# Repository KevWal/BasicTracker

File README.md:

# BasicTracker
Light weight long run time cheap tracker

# Hardware

## Power
Single AA or AAA cell, 0.8v to 1.6v input range - TPS61200 to boost to 1.8 or 3.3v

Solar Panel, 0.5v to 4.2v input range - either connect direct or use TPS61200 to boost or limit or MCP1700T to limit to 1.8 or 3.3v

Single AA or AAA cell and Solar Panel, needs 2 x MAX40200 ideal diodes to keep supplies separate and TPS61200 to boost or limit to 1.8v or 3.3v
	Primary cells will keep tracker going over night till battery runs out

Single Lithium, 2.8v to 4.2v useful range, needs Battery Protection on Lipo to limit min discharge voltage and MCP1700T to limit to 1.8 or 3.3v
	Will likely freeze at night

Single Lithium and Solar Panel, Solar Panel needs TPS61200 to stop lithium discharging through it and buck/boost voltage to max 4.2v for Lithium charging.  Lithium needs Battery Protection to limit min discharge voltage and MCP1700T to limit to 1.8 or 3.3v. Lithium will likely freeze at night.

### Boost Converter
Boost converter to 1.8v with 3.3v and 4.2v (for lithium charge) option

Step ups in stock with JLC:
L6920DBTR - $1.40 RP Protect, Min startup for 3.3vout@40mA = 0.72v
TPS61220DCKR - $0.49 Min startup for 3.3vout@40mA = 0.7v
TLV61220DBVR - $0.26. Min startup for 3.3vout@40mA = 0.7v
*TPS61200DRC - $0.85.  Min startup for 3.3vout@40mA = 0.4v, max 150mA at 0.7v in*

#### Inductor
*SMD_Murata-Electronics-1227AS-H-2R2M-P2_C435389*

### Voltage Measuring
Measure Battery, Solar and Lithium voltages

## GPS Module
Ublox Max 6G 1.75v to 2.0v
Ublox Max 7C / M8C 1.65v to 3.6v
Ublox Max M8Q 2.7v to 3.6v

ATGM336N 2.7v to 3.6v.
Quectel L70 2.8v to 4.3v

Connected I2C, PPS, Battery Backup, etc
Battery backup via resistor, capacitor and diode
Antenna Options - Chip, Wire, static leak resister option

### GPS Power Switch
*SIP32431DR3-T1GE3 - instock in JLC*

### GPS Filtering
*MuRata_BLM15HD102SN1D_1kR-25-at100MHz-250mA_C21516*

### GPS Antenna
1/4 wave wire = 45.2mm (1575Mhz) (1/4 wave generally better than chip antenna IMO)

## Processor
ATMega1284p - In stock in JLC, 10mmx10mm, 128kb of storage, 16kb of ram
	Step up from 328 but still same family
	JTAG interface not one wire debug.
	Info on using the 1284 - https://prominimicros.com/
	Arduino Core - https://github.com/MCUdude/MightyCore
4Mhz crystal (max at 1.8v) and option to use /8 fuse.

Move to a ATSAMD21G18A-AU or similar?  Still arduinio compatible but so much more powerful.
	ARM Cortex SWD interface?  Built in RTC.  Not instock with JLC

STM xx?
Ideally would get a USB Interface, but no easy in JLC stock way found.

### Crystal
XXFEELNANF-14.7456M & 16pF.  Divide by 8 to get 1.843200Mhz and use 115,200 comms

## Fuses
Extended = 0xFF
High = 0x16
Low = 0x7F (ck div 8 set)

Arduino
	Clock External 14.7456 (even though clk/8 fuse set)?

## Radio
SX1278 (137-525MHz) on the DORJI DRF1278F module - http://www.dorji.com/products-detail.php?ProId=14
	1.8v to 3.6v, < 1uA standby

or

Hope RF RFM98W - 433MHz band
https://www.hoperf.com/modules/lora/RFM98.html
	1.8v to 3.7v, < 1uA standby

# IDE
Move away from Arduinio V1?

Mightcore for ATMega1284p - https://github.com/MCUdude/MightyCore

Arduino V2 - https://www.arduino.cc/en/Tutorial/getting-started-with-ide-v2
Visual Micro - Arduino for Visual Studio - https://www.visualmicro.com/
PlatformIO IDE - Arduino and Visual Studio Code - https://platformio.org/

## Arduino V2
Too add the AVR Dragon programmer, add the below to:

C:\Users\WALTONK\AppData\Local\Arduino15\packages\MightyCore\hardware\avr\2.1.2\programmers.txt

dragon_jtag.name=Dragon JTAG (KW)
dragon_jtag.communication=usb
dragon_jtag.protocol=dragon_jtag
dragon_jtag.program.protocol=dragon_jtag
dragon_jtag.program.tool=avrdude
dragon_jtag.program.extra_params=-P usb

## Microchip Studio
Good Device Programming interface for fuses
Works with:
	Pololu USB AVR (STK500) - can supply / program at 3.3 or 5v; and
	AVR Dragon - can supply 5v, can program down to 1.8v

# Others Projects
UPU's original 1.8v 4Mhz - https://ava.upuaut.net/?p=383 https://ava.upuaut.net/?p=353
	RFM22B

# Code Research
Dave's flexavr - https://github.com/daveake/flexavr
	Designed for Standalone AVR attached to a Pi Zero
	APRS via PWM to radio module, LoRa via RFM98W (sx1278, no library, direct register writes), Some RTTY functions, but doesn't seem complete?

OK1CDJ Picotracker - https://github.com/ok1cdj/Picotracker/blob/master/sw/picotracker.ino
	RTTY via RFM22 only, but useful power saving code.

Dave's FlexTrack - https://github.com/daveake/FlexTrack
	APRS via PWM to radio module, RTTY via Radiometrix MTX2 or Lora, LoRa via RFM98W (sx1278) 
	No library, direct register writes, spread across multiple ino's
	Onboard landing position prediction
	
Dave's FlexTrack TTGO - https://github.com/daveake/FlexTrack_TTGO
	As above, designed for TTGO board, LoRa & RTTY

*RoelKroes TB Tracker -  https://github.com/RoelKroes/TBTracker*
	RTTY and LoRa via SX127x (or Hope RFM9x)
	Uses RadioLib - https://github.com/jgromes/RadioLib and tinyGPS++ https://github.com/mikalhart/TinyGPSPlus
		Radiolib supports SX126/7/8x, RFM9x and many others, supports RTTY, Morse, SSTV, Hellschreiber, LoRa and support for LoRaWAN and APRS in discussion, but complex
	Has sleep functionality, nicely laid out

Stuarts HAB2 code - https://github.com/StuartsProjects/HAB2
	RTTY and Lora via SX126/7/8x
	Uses Stuarts SX12XX Library https://github.com/StuartsProjects/SX12XX-LoRa
	All in a single .ino and .h
	Has Upload command capability, Sleep, EEPROM config complexity
	Looks like the one file does command mode upload and tracker functionality

## The Things Network (TTN)
How about TTN upload too?

https://www.thethingsnetwork.org/docs/lorawan/frequency-plans/
EU 868, US 902, CN 470, AU 915, AS 923, etc

Steve G8KHW did a tracker based on xx but cant find the code?
	https://groups.google.com/g/ukhas/c/SxUo0VpO1XQ/m/mD6qNCW9BgAJ
	
Stuarts TTN code: https://github.com/StuartsProjects/TTN_GPS_Tracker
	Based on https://www.thethingsnetwork.org/labs/story/lorawan-gsp-tracker
	Uses the ATmega328P, RFM98 & LMIC library

Junior IOT code: https://github.com/JuniorIOT/GPS-Lora-Balloon-rfm95-TinyGPS
	Uses the ATmega328P, RFM95 & LMIC library
	
Nick's example of LMIC library on a 328p
	https://github.com/descartes/Arduino-LMIC-example
	
LMIC library https://github.com/matthijskooijman/arduino-lmic
	Supports SX1272 and SX1276 families (inc RFM92 and RFM95)
	
Adafruit TTN library: https://github.com/adafruit/TinyLoRa/

ICSpace Multi region TTN Tracker - https://github.com/ImperialSpaceSociety/picotracker-Lora
	Uses Murata ABZ LoRa Module (STM32 and LoRa radio combined)
	Updated TTNHABBridge - https://github.com/ImperialSpaceSociety/ttnhabbridge

Draguinio STM32 based TTN Tracker - https://www.tindie.com/products/edwin/lorawan-gps-tracker-with9-axis-accelerometer-lgt92/

http://revspace.nl/TTNHABBridge for uploader to HabHub

Needs dedicated LoraWAN reciever like:
Or could use LoRaGateway with this:  https://github.com/bokse001/dual_chan_pkt_fwd

## APRS
Can't do airbourne in the UK or on a UK call sign, 144Mhz, licensed spectrum

## Issues
Want to do RTTY, LoRa, APRS & LoRaWAN (TTN) from the same tracker.
LoRa HAB and RTTY are best done on 433Mhz license free, although could be done on 868Mhz
LoRaWAN has to be done on 868Mhz license free in Europe
APRS is on 144Mhz

HopeRF modules dont seem to have lower and upper band outputs connected to aerial?
RadioLib doesn't do APRS or LoRaWAN

## LoRa Modes

### From lora-gateway code:
Num; ImplicitOrExplicit; ErrorCoding; Bandwidth; SpreadingFactor; LowDataRateOptimize; BaudRate; Description
0: EXPLICIT_MODE, ERROR_CODING_4_8, BANDWIDTH_20K8, SPREADING_11, 1,    60, Telemetry - Normal mode for telemetry
1: IMPLICIT_MODE, ERROR_CODING_4_5, BANDWIDTH_20K8, SPREADING_6,  0,  1400, SSDV - Normal mode for SSDV
2: EXPLICIT_MODE, ERROR_CODING_4_8, BANDWIDTH_62K5, SPREADING_8,  0,  2000, Repeater - Normal mode for repeater network	
3: EXPLICIT_MODE, ERROR_CODING_4_6, BANDWIDTH_250K, SPREADING_7,  0,  8000, Turbo - Normal mode for high speed images in 868MHz band
4: IMPLICIT_MODE, ERROR_CODING_4_5, BANDWIDTH_250K, SPREADING_6,  0, 16828, TurboX - Fastest mode within IR2030 in 868MHz band
5: EXPLICIT_MODE, ERROR_CODING_4_8, BANDWIDTH_41K7, SPREADING_11, 0,   200, Calling - Calling mode
6: EXPLICIT_MODE, ERROR_CODING_4_5, BANDWIDTH_20K8, SPREADING_7,  0,  2800, Uplink - Uplink explicit mode (variable length)
7: IMPLICIT_MODE, ERROR_CODING_4_5, BANDWIDTH_41K7, SPREADING_6,  0,  2800, Uplink - Uplink mode for 868
8: EXPLICIT_MODE, ERROR_CODING_4_5, BANDWIDTH_20K8, SPREADING_7,  0,   910, Telnet - Telnet-style comms with HAB on 434
9: IMPLICIT_MODE, ERROR_CODING_4_5, BANDWIDTH_62K5, SPREADING_6,  0,  4500, SSDV Repeater - Fast (SSDV) repeater network

# Launch Announcement

Also testing some backup trackers:

Hoping to do a launch on Sunday (20th, tomorrow) morning, before 9am GMT from Northamptonshire, UK of a Yokohama Balloon, carrying a custom built 'Single AA' tracker based originally on the TBTracker code base, but heavily expanded and modified.

Looking to A) test my ability to get a Yokohama to float, and B) the custom tracker being able to be decoded across RTTY, LoRa and Horus FSK4.  Flight path is predicted to take it across Holland, Germany & maybe Poland - but with the weather systems all over the place at the moment, who knows! :)

The tracker is based on the ATmega1284 running at 1.8432Mhz, Ublox GPS and DRF1278 radio module, all with a 1.8v VCC.  About 25g with 1 x AA.

Yokohama is 48.6g and was pre stretched at 0.22PSI up to about 99" circumference and filled to 6g of free lift.

RTTY - KW-BCK1 - 50 Baud, 8n2, 610Hz shift, 434.113Mhz, 1 short sentence repeated 3 times every once every 2 minutes
	RX Frequency for me was about 434.084Mhz

LoRa - KW-BCK2 - Mode 5, 433.650Mhz, 1 sentence repeated 3 times every once every 2 minutes
	Field String of 0123456AI9, RX frequency for me of 433.653

Horus FSK4 - G7PMO-V2 - 100 Baud, 244Hz shift, 434.340Mhz, 1 binary packet repeated 3 times every once every 2 minutes
	RX frequency for me was about 434.312Mhz
	
Weight

28g + 6g free lift = 34

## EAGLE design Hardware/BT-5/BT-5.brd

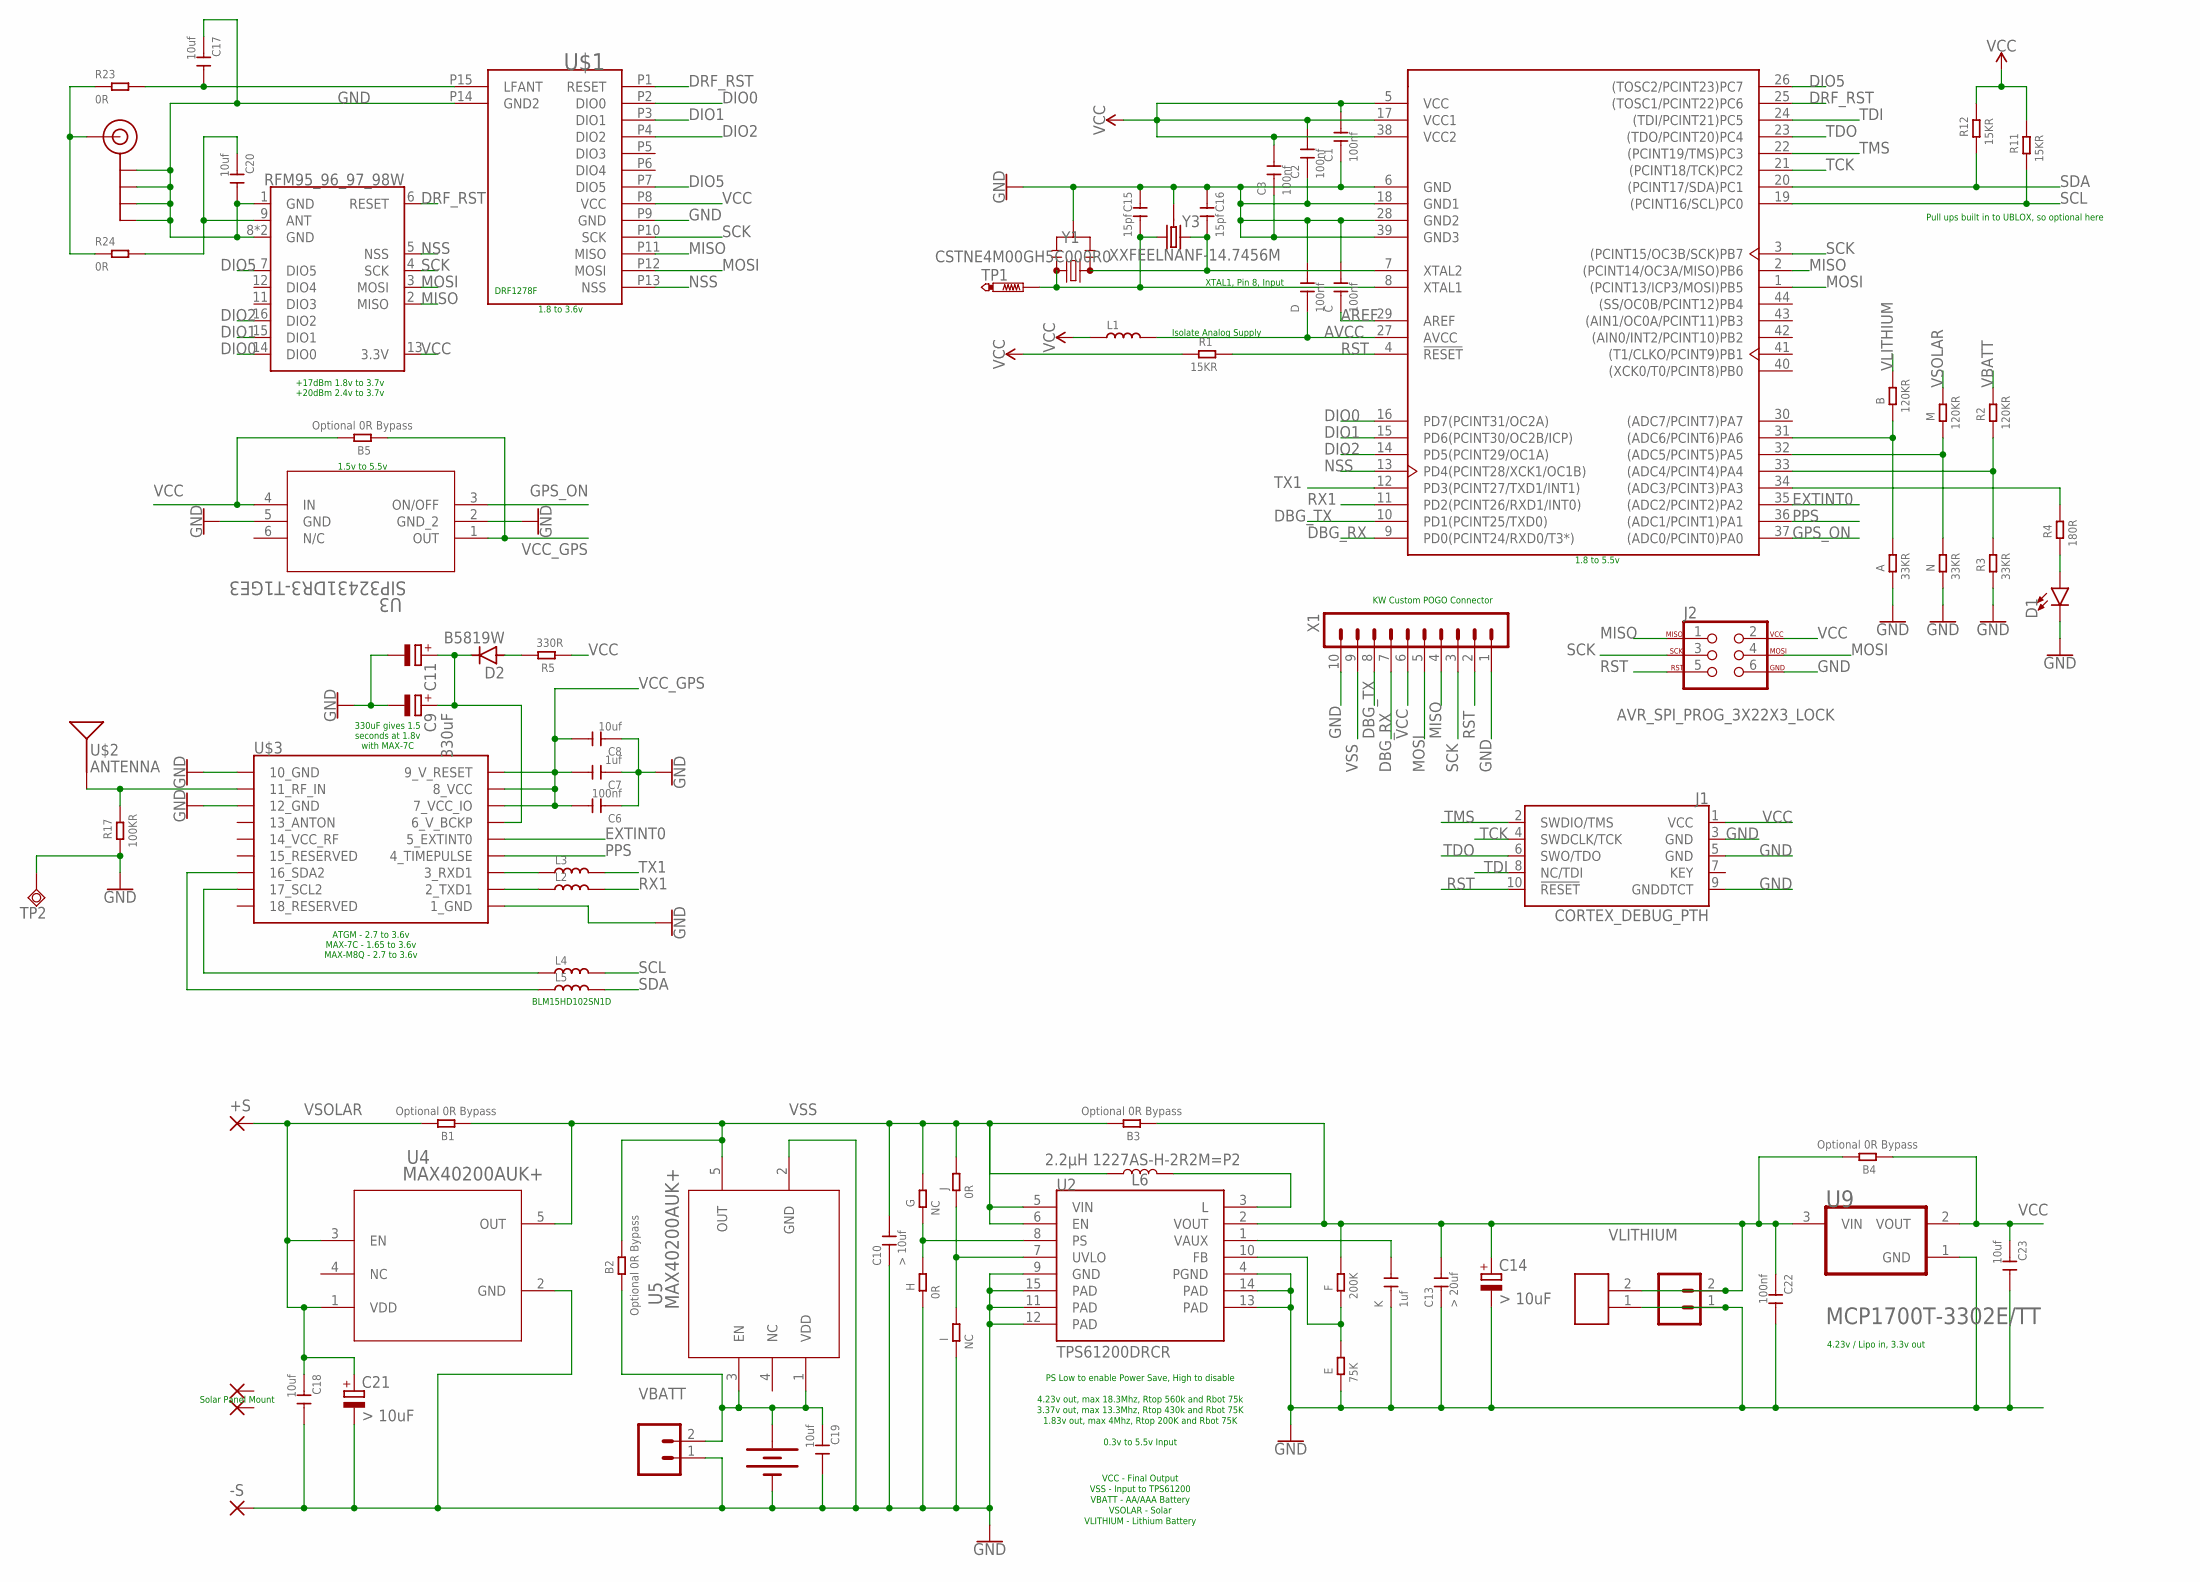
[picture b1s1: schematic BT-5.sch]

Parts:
+S: SMD2; SMD1,27-2,54
-S: SMD2; SMD1,27-2,54
A: 33KR; R0402
B: 120KR; R0402
B1, B2, B3, B4, B5: Optional 0R Bypass; R0402
BT1: BATTERY; BATTERY-AA-AAA
C, C1, C2, C3, C6, C22: 100nf; C0402
C7: 1uf; C0402
C8, C17, C18, C19, C20, C23: 10uf; C0402
C9: 330uF; RCL_SMC_C
C10: > 10uf; C0603
C11: C-POL_ECAP-10.5MM; CAPAE1030X1050N
C13: > 20uf; C0603
C14, C21: > 10uF; RCL_SMC_C
C15, C16: 15pf; C0402
D: 100nf; C0402
D1: LED0603; LED-0603
D2: B5819W; SOD123; LCSC_PART C8598
E: 75K; R0402
F: 200K; R0402
G: NC; R0402
H: 0R; R0402
I: NC; R0402
J: 0R; R0402
J1: CORTEX_DEBUG_PTH; 2X5-PTH-1.27MM
J2: AVR_SPI_PROG_3X22X3_LOCK; 2X3_LOCK
J4, J6: CONN_02JST-PTH-2-KIT; JST-2-PTH-KIT
J5: JST_ZH_2PIN
J$1: SMA_EDGE; SMA-EDGE
K: 1uf; C0402
L1, L2, L3, L4, L5: BLM15HD102SN1D; L0402
L6: 2.2µH 1227AS-H-2R2M=P2; INDUCTOR_4.7UH; LCSC_PART C435389
M: 120KR; R0402
N: 33KR; R0402
NC1, NC2: SMD2; SMD1,27-2,54
R1, R11, R12: 15KR; R0402
R2: 120KR; R0402
R3: 33KR; R0402
R4: 180R; R0402
R5: 330R; R0402
R17: 100KR; R0402
R23, R24: 0R; R0603
TP1: TESTPAD_PTR1TP10R; TESTPAD_TP10R
TP2: TPSQTP08SQ; TP08SQ
U1: ATMEGA1284P-AU; TQFP-44; LCSC_PART C33575
U2: TPS61200DRCR; QFN-10_PAD; LCSC_PART C140320
U3: SIP32431DR3-T1GE3; SC-70-6_VIS; LCSC_PART C141606
U4, U5: MAX40200AUK+; RAJX_V4.5_REVA_21-0057F_MXM
U6: RFM95_96_97_98W; RFM69HCW-XXXS2
U9: MICROCHIP_MCP1700T-3302E-TTMICROCHIP_MCP1700T-330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; MICROCHIP_MCP1700T-3302E-TT_0
U$1: DRF1278F; DRF1278F_2_NO_PINS
U$2: ANTENNA; ANT-GPS-3X10MM
U$3: AVA_UBLOX_MAX-6
X1: KEW_HF_V13_M_1R10KW_50MIL-H; KEW_HF_V13_M_1R09_50MIL-H
Y1: CSTNE4M00GH5C000R0; SPARKFUN-CLOCKS-KW_RESONATOR-SMD-3.2X1.3
Y3: XXFEELNANF-14.7456M; CRYSTAL-SMD-3.2X2.5MM; LCSC_PART C124311

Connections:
AREF: C.1, U1.29 (AREF)
AVCC: D.1, L1.2, U1.27 (AVCC)
DBG_RX: U1.9 (PD0(PCINT24/RXD0/T3*)), X1.7
DBG_TX: U1.10 (PD1(PCINT25/TXD0)), X1.8
DIO0: U1.16 (PD7(PCINT31/OC2A)), U6.14 (DIO0), U$1.P2 (DIO0)
DIO1: U1.15 (PD6(PCINT30/OC2B/ICP)), U6.15 (DIO1), U$1.P3 (DIO1)
DIO2: U1.14 (PD5(PCINT29/OC1A)), U6.16 (DIO2), U$1.P4 (DIO2)
DIO5: U1.26 ((TOSC2/PCINT23)PC7), U6.7 (DIO5), U$1.P7 (DIO5)
DRF_RST: U1.25 ((TOSC1/PCINT22)PC6), U6.6 (RESET), U$1.P1 (RESET)
EXTINT0: U1.35 ((ADC2/PCINT2)PA2), U$3.5_EXTINT0
FB: E.2, F.1, U2.10 (FB)
GND: -S.1, A.1, BT1.P$2 (-), BT1.P$4 (-), BT1.P$7 (-), BT1.P$8 (-), C.2, C1.1, C2.1, C3.1, C6.1, C7.1, C8.1, C9.-, C10.1, C11.2 (-), C13.1, C14.-, C15.2, C16.2, C17.1, C18.2, C19.2, C20.2, C21.-, C22.2, C23.2, D.2, D1.C, E.1, H.1, I.1, J1.3 (GND), J1.5 (GND), J1.9 (GNDDTCT), J2.6, J4.1, J5.1, J6.1, J$1.GND@0 (GND), J$1.GND@1 (GND), J$1.GND@2 (GND), J$1.GND@3 (GND), K.1, N.1, R3.1, R17.1, TP2.TP, U1.6 (GND), U1.18 (GND1), U1.28 (GND2), U1.39 (GND3), U2.4 (PGND), U2.9 (GND), U2.11 (PAD), U2.12 (PAD), U2.13 (PAD), U2.14 (PAD), U2.15 (PAD), U3.2 (GND_2), U3.5 (GND), U4.2 (GND), U5.2 (GND), U6.1 (GND), U6.8 (GND), U6.10 (GND), U9.1 (GND), U$1.P9 (GND), U$1.P14 (GND2), U$3.1_GND, U$3.10_GND, U$3.12_GND, X1.1, X1.10, Y1.2, Y3.2 (3), Y3.4 (3)
GPS_ON: U1.37 ((ADC0/PCINT0)PA0), U3.3 (ON/OFF)
L: L6.P$2 (2), U2.3 (L)
MISO: J2.1, U1.2 ((PCINT14/OC3A/MISO)PB6), U6.2 (MISO), U$1.P11 (MISO), X1.4
MOSI: J2.4, U1.1 ((PCINT13/ICP3/MOSI)PB5), U6.3 (MOSI), U$1.P12 (MOSI), X1.5
unnamed: C17.2, R23.2, U$1.P15 (LFANT)
unnamed: D1.A, R4.1
unnamed: C15.1, TP1.TP, U1.8 (XTAL1), Y1.3, Y3.3 (2)
unnamed: C16.1, U1.7 (XTAL2), Y1.1, Y3.1
unnamed: R2.1, R3.2, U1.33 ((ADC4/PCINT4)PA4)
unnamed: M.1, N.2, U1.32 ((ADC5/PCINT5)PA5)
unnamed: R4.2, U1.34 ((ADC3/PCINT3)PA3)
unnamed: R17.2, U$2.SIG, U$3.11_RF_IN
unnamed: C9.+, C11.1 (+), D2.C, U$3.6_V_BCKP
unnamed: L3.1, U$3.3_RXD1
unnamed: L2.1, U$3.2_TXD1
unnamed: L4.1, U$3.17_SCL2
unnamed: L5.1, U$3.16_SDA2
unnamed: D2.A, R5.2
unnamed: A.2, B.1, U1.31 ((ADC6/PCINT6)PA6)
unnamed: C20.1, R24.2, U6.9 (ANT)
unnamed: J$1.SIG (SIGNAL), R23.1, R24.1
NSS: U1.13 (PD4(PCINT28/XCK1/OC1B)), U6.5 (NSS), U$1.P13 (NSS)
PPS: U1.36 ((ADC1/PCINT1)PA1), U$3.4_TIMEPULSE
PS: G.1, H.2, U2.8 (PS)
RST: J1.10 (!RESET), J2.5, R1.2, U1.4 (!RESET), X1.2
RX1: L2.2, U1.11 (PD2(PCINT26/RXD1/INT0))
SCK: J2.3, U1.3 ((PCINT15/OC3B/SCK)PB7), U6.4 (SCK), U$1.P10 (SCK), X1.3
SCL: L4.2, R11.1, U1.19 ((PCINT16/SCL)PC0)
SDA: L5.2, R12.1, U1.20 ((PCINT17/SDA)PC1)
TCK: J1.4 (SWDCLK/TCK), U1.21 ((PCINT18/TCK)PC2)
TDI: J1.8 (NC/TDI), U1.24 ((TDI/PCINT21)PC5)
TDO: J1.6 (SWO/TDO), U1.23 ((TDO/PCINT20)PC4)
TMS: J1.2 (SWDIO/TMS), U1.22 ((PCINT19/TMS)PC3)
TX1: L3.2, U1.12 (PD3(PCINT27/TXD1/INT1))
UVLO: I.2, J.1, U2.7 (UVLO)
VAUX: K.2, U2.1 (VAUX)
VBATT: B2.1, BT1.P$1 (+), BT1.P$3 (+), BT1.P$5 (+), BT1.P$6 (+), C19.1, J4.2, R2.2, U5.1 (VDD), U5.3 (EN)
VCC: B4.1, B5.2, C1.2, C2.2, C3.2, C23.1, J1.1 (VCC), J2.2, L1.1, R1.1, R5.1, R11.2, R12.2, U1.5 (VCC), U1.17 (VCC1), U1.38 (VCC2), U3.4 (IN), U6.13 (3.3V), U9.2 (VOUT), U$1.P8 (VCC), X1.6
VCC_GPS: B5.1, C6.2, C7.2, C8.2, U3.1 (OUT), U$3.7_VCC_IO, U$3.8_VCC, U$3.9_V_RESET
VLITHIUM: B.2, B3.1, B4.2, C13.2, C14.+, C22.1, F.2, J5.2, J6.2, U2.2 (VOUT), U9.3 (VIN)
VSOLAR: +S.1, B1.2, C18.1, C21.+, M.2, U4.1 (VDD), U4.3 (EN)
VSS: B1.1, B2.2, B3.2, C10.2, G.2, J.2, L6.P$1 (1), U2.5 (VIN), U2.6 (EN), U4.5 (OUT), U5.5 (OUT), X1.9

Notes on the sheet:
XTAL1, Pin 8, Input
Isolate Analog Supply
KW Custom POGO Connector
DRF1278F
1.8 to 3.6v
1.8 to 5.5v
ATGM - 2.7 to 3.6v MAX-7C - 1.65 to 3.6v MAX-M8Q - 2.7 to 3.6v
Pull ups built in to UBLOX, so optional here
BLM15HD102SN1D
PS Low to enable Power Save, High to disable 4.23v out, max 18.3Mhz, Rtop 560k and Rbot 75k 3.37v out, max 13.3Mhz, Rtop 430k and Rbot 75K 1.83v out, max 4Mhz, Rtop 200K and Rbot 75K 0.3v to 5.5v Input
Solar Panel Mount
VCC - Final Output VSS - Input to TPS61200 VBATT - AA/AAA Battery VSOLAR - Solar VLITHIUM - Lithium Battery
1.5v to 5.5v
+17dBm 1.8v to 3.7v +20dBm 2.4v to 3.7v
4.23v / Lipo in, 3.3v out
330uF gives 1.5 seconds at 1.8v with MAX-7C

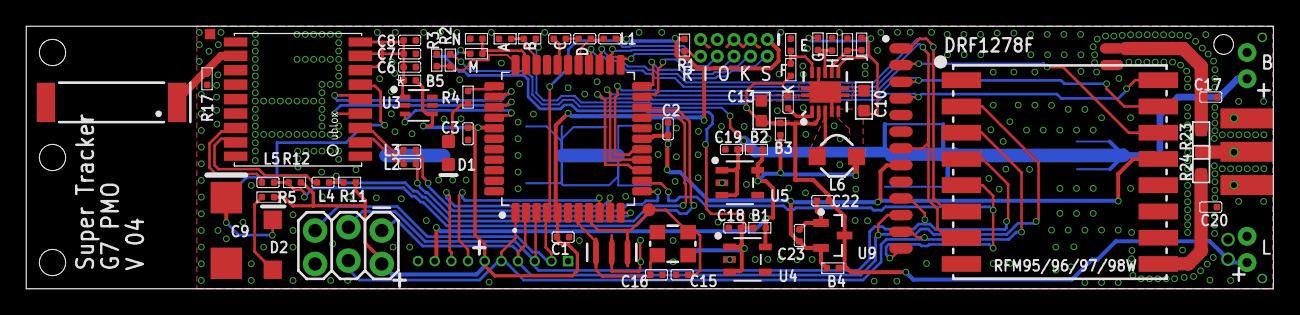
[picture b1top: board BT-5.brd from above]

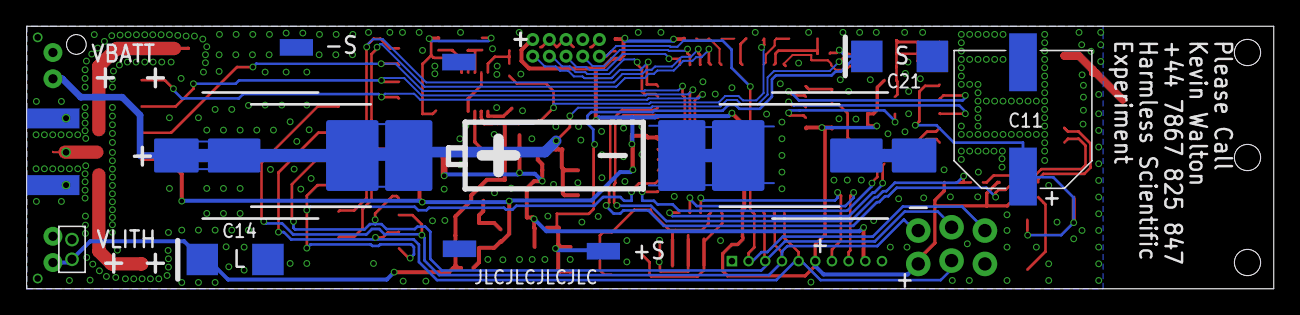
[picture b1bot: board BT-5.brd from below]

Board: 2 copper layers, 95.0 x 20.0 mm, 82 parts (11 on the bottom side), 54 nets.

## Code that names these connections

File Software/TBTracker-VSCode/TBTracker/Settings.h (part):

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*  
* Change if needed
************************************************************************************/
#define PIN_NSS   PIN_PD4
#define PIN_DIO0  PIN_PD7
#define PIN_RESET PIN_PC6
#define PIN_DIO1  PIN_PD6


/***********************************************************************************
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// This will only work when USE_DEEP_SLEEP=true and there is a valid GPS lock.
// Comment out the pins you use for your sensors or leds. 
// Set pin value to a valid value.
#define POWER_PIN1     PIN_PA0
// #define POWER_PIN2     4
// #define POWER_PIN3     -1
// #define POWER_PIN4     -1
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#define DEVMODE // Development mode. Uncomment to enable for debugging and see debug info on the serial monitor
#define DBGBAUD 115200
#define SERIALDBG Serial
#define LED PIN_PA3

       
/***********************************************************************************
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#define USE_EXTERNAL_VOLTAGE true  // Set to true if you want to measure an external voltage on the EXTERNALVOLTAGE_PIN 
#define VCC_OFFSET 0.00            // Offset for error correction in Volts for the internal voltage. Ideally this should be 0.0 but usually is between -0.1 and +0.1 and is chip specific. 
#define EXT_OFFSET 0.00            // Offset for error correction in Volts for the external voltage. Use it to correct errors when necessary.
#define EXTERNALVOLTAGE_PIN PIN_PA4     // Pin to read the external voltage from
#define SAMPLE_RES 1024            // 1024 for Uno, Mini, Nano, Mega, Micro. Leonardo. 4096 for Zero, Due and MKR  
#define DIVIDER_RATIO 4.636        // Leave at 1.00 when using no voltage divider. Set to (R1+R2)/R2 when using a voltage divider. (120+33)/33

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
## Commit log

2021-04-28 Move to BT-2
2021-05-16 Sent to JLC
2021-05-16 Added TB Tracker
2021-05-21 Correcting Markdown
2022-09-25 First Commit TBTracker for PlatformIO
2022-09-26 Generic .gitignore update
2022-10-05 Changes in progress
2022-10-23 Software updates
2022-11-05 Added RTTY Interrupt based code

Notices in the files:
parts and their libraries:
SparkFun-Connectors: Licensing: Creative Commons ShareAlike 4.0 International - https://creativecommons.org/licenses/by-sa/4.0
COPYRIGHT: Copyright (C) 2018 Accelerated Designs. All rights reserved
